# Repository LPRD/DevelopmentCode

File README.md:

# DevelopmentCode
A place to put all our code for messing around and developing things

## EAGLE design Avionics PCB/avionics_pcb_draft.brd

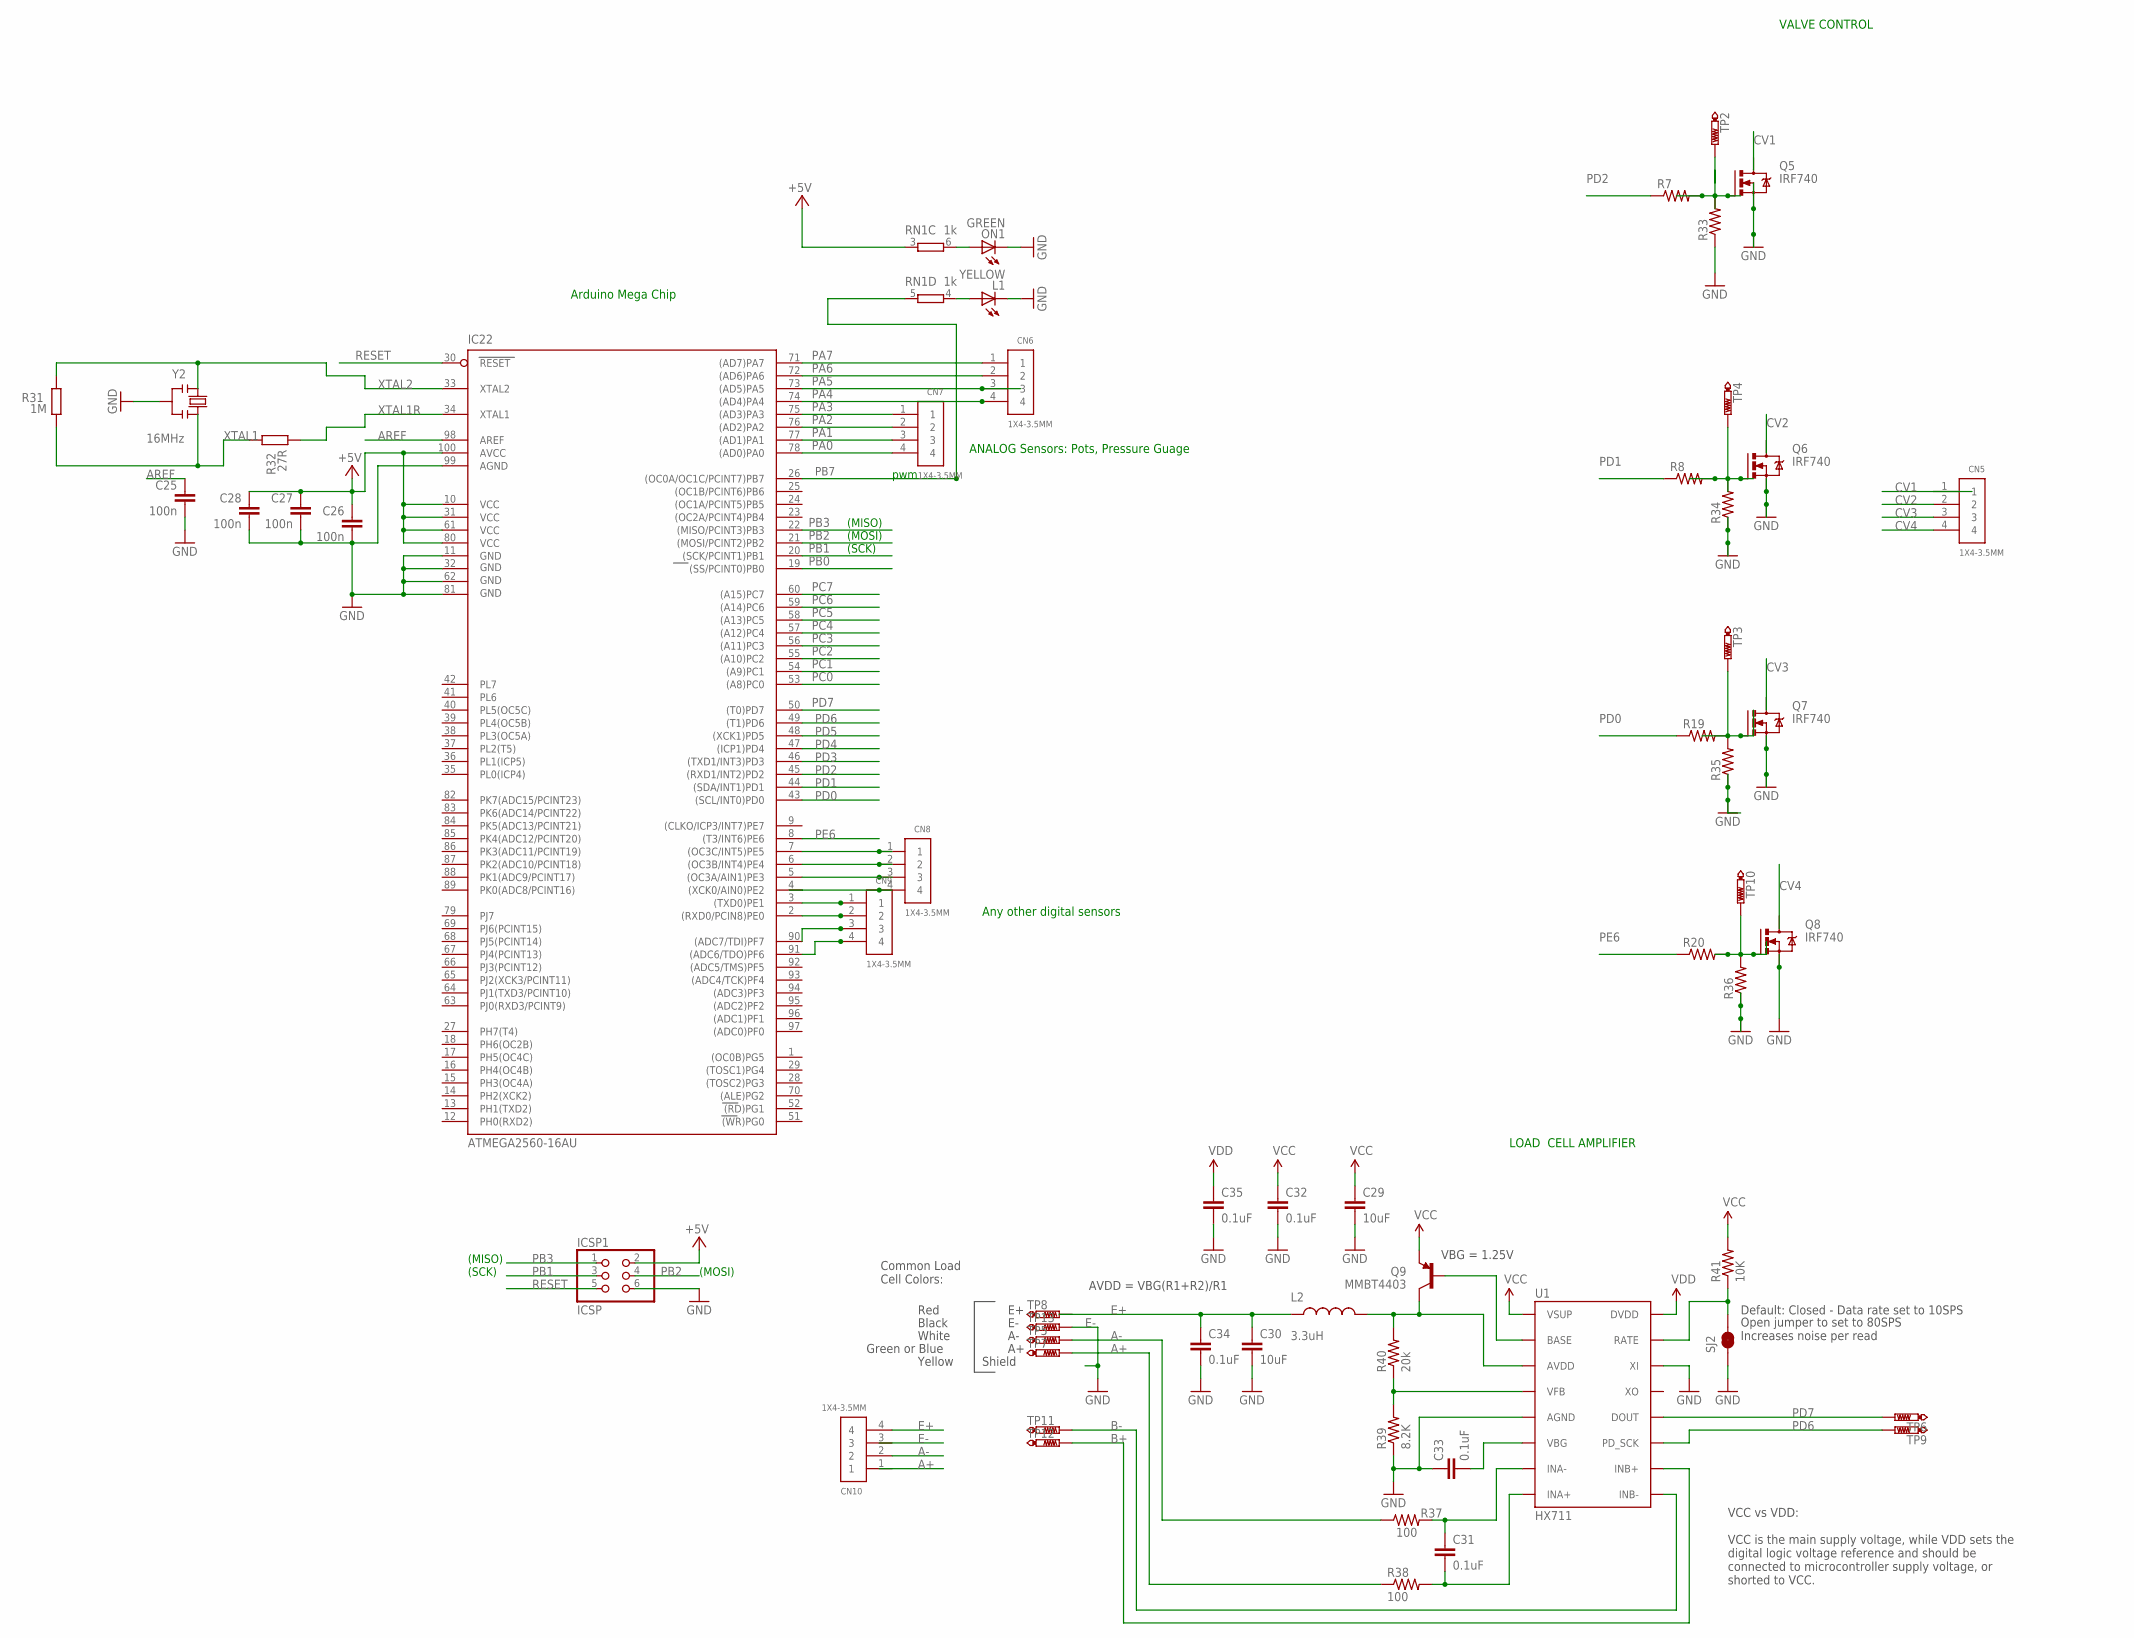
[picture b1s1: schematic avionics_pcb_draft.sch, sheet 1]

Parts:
C25, C26, C27, C28: 100n; C0603-ROUND
C29, C30: 10uF; 1210
C31, C32, C33, C34, C35: 0.1uF; 0603-CAP
CN5, CN6, CN7, CN8, CN9, CN10: 1X4-3.5MM; 1X04-3.5MM
IC22: ATMEGA2560-16AU; TQFP100
ICSP1: ICSP; 2X03
L1: YELLOW; CHIP-LED0805
L2: 3.3uH; 0805
ON1: GREEN; CHIP-LED0805
Q5, Q6, Q7, Q8: IRF740; TO220BV
Q9: MMBT4403; SOT23-3
R7, R8, R19, R20, R33, R34, R35, R36: R-US_R0805; R0805
R31: 1M; R0603-ROUND
R32: 27R; R0603-ROUND
R37, R38: 100; 0603-RES
R39: 8.2K; 0603-RES
R40: 20k; 0603-RES
R41: 10K; 0603-RES
RN1: 1k; CAY16
SJ2: JUMPER-PAD-2-NC_BY_TRACE; PAD-JUMPER-2-NC_BY_TRACE_YES_SILK
TP2, TP3, TP4, TP5, TP6, TP7, TP8, TP9, TP10, TP11, TP12, TP13: PTR1B1,27; B1,27
U1: HX711; SO16
Y2: 16MHz; RESONATOR

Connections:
+5V: C26.1, C27.1, C28.1, IC22.10 (VCC), IC22.31 (VCC1), IC22.61 (VCC2), IC22.80 (VCC3), IC22.100 (AVCC), ICSP1.2, RN1.3 (1); also elsewhere on the board
A+: R38.1, TP7.TP
A-: CN10.2, R37.1, TP5.TP
AREF: C25.1, IC22.98 (AREF)
B+: TP12.TP, U1.10 (INB+)
B-: TP11.TP, U1.9 (INB-)
CV1: CN5.1
CV2: CN5.2
CV3: CN5.3
CV4: CN5.4
E+: C30.1, C34.1, CN10.4, L2.1, TP8.TP
E-: TP13.TP
GND: C25.2, C26.2, C27.2, C28.2, C29.2, C30.2, C32.2, C33.1, C34.2, C35.2, IC22.11 (GND), IC22.32 (GND1), IC22.62 (GND2), IC22.81 (GND3), IC22.99 (AGND), ICSP1.6, L1.C, ON1.C, Q5.S, Q6.S, Q7.S, Q8.S, R33.1, R34.1, R39.1, SJ2.1, U1.5 (AGND), U1.14 (XI), Y2.2; also elsewhere on the board
unnamed: CN8.1, IC22.7 ((OC3C/INT5)PE5)
unnamed: CN8.2, IC22.6 ((OC3B/INT4)PE4)
unnamed: CN8.3, IC22.5 ((OC3A/AIN1)PE3)
unnamed: CN8.4, IC22.4 ((XCK0/AIN0)PE2)
unnamed: Q5.G, R7.2, R33.2
unnamed: Q6.G, R8.2, R34.2
unnamed: CN9.1, IC22.3 ((TXD0)PE1)
unnamed: CN9.2, IC22.2 ((RXD0/PCIN8)PE0)
unnamed: CN9.3, IC22.90 ((ADC7/TDI)PF7)
unnamed: CN9.4, IC22.91 ((ADC6/TDO)PF6)
unnamed: Q7.G, R19.2, R35.2, TP3.TP
unnamed: Q8.G, R20.2, R36.2, TP10.TP
unnamed: ON1.A, RN1.6 (2)
unnamed: L1.A, RN1.4 (1)
unnamed: Q9.1 (B), U1.2 (BASE)
unnamed: R39.2, R40.1, U1.4 (VFB)
unnamed: C33.2, U1.6 (VBG)
unnamed: L2.2, Q9.3 (C), R40.2, U1.3 (AVDD)
unnamed: R41.1, SJ2.2, U1.15 (RATE)
unnamed: C31.1, R37.2, U1.7 (INA-)
unnamed: C31.2, R38.2, U1.8 (INA+)
PA0: CN7.4, IC22.78 ((AD0)PA0)
PA1: CN7.3, IC22.77 ((AD1)PA1)
PA2: CN7.2, IC22.76 ((AD2)PA2)
PA3: CN7.1, IC22.75 ((AD3)PA3)
PA4: CN6.4, IC22.74 ((AD4)PA4)
PA5: CN6.3, IC22.73 ((AD5)PA5)
PA6: CN6.2, IC22.72 ((AD6)PA6)
PA7: CN6.1, IC22.71 ((AD7)PA7)
PB0: IC22.19 ((SS/PCINT0)PB0)
PB1: IC22.20 ((SCK/PCINT1)PB1), ICSP1.3
PB2: IC22.21 ((MOSI/PCINT2)PB2), ICSP1.4
PB3: IC22.22 ((MISO/PCINT3)PB3), ICSP1.1
PB7: IC22.26 ((OC0A/OC1C/PCINT7)PB7), RN1.5 (2)
PC0: IC22.53 ((A8)PC0)
PC1: IC22.54 ((A9)PC1)
PC2: IC22.55 ((A10)PC2)
PC3: IC22.56 ((A11)PC3)
PC4: IC22.57 ((A12)PC4)
PC5: IC22.58 ((A13)PC5)
PC6: IC22.59 ((A14)PC6)
PC7: IC22.60 ((A15)PC7)
PD0: IC22.43 ((SCL/INT0)PD0), R19.1
PD1: IC22.44 ((SDA/INT1)PD1), R8.1
PD2: IC22.45 ((RXD1/INT2)PD2), R7.1
PD3: IC22.46 ((TXD1/INT3)PD3); also elsewhere on the board
PD4: IC22.47 ((ICP1)PD4); also elsewhere on the board
PD5: IC22.48 ((XCK1)PD5); also elsewhere on the board
PD6: IC22.49 ((T1)PD6), TP9.TP, U1.11 (PD_SCK)
PD7: IC22.50 ((T0)PD7), TP6.TP, U1.12 (DOUT)
PE6: IC22.8 ((T3/INT6)PE6), R20.1
RESET: IC22.30 (RESET), ICSP1.5
VCC: C29.1, C32.1, Q9.2 (E), R41.2, U1.1 (VSUP)
VDD: C35.1, U1.16 (DVDD)
XTAL1: R31.1, R32.2, Y2.3
XTAL1R: IC22.34 (XTAL1), R32.1
XTAL2: IC22.33 (XTAL2), R31.2, Y2.1

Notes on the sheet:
(SCK)
(MISO)
(MOSI)
pwm
VBG = 1.25V
AVDD = VBG(R1+R2)/R1
Default: Closed - Data rate set to 10SPS
Open jumper to set to 80SPS Increases noise per read
Red
Black
White
Green or Blue
Common Load Cell Colors:
Shield
Yellow
VCC vs VDD: VCC is the main supply voltage, while VDD sets the digital logic voltage reference and should be connected to microcontroller supply voltage, or shorted to VCC.
Arduino Mega Chip
LOAD CELL AMPLIFIER
VALVE CONTROL
ANALOG Sensors: Pots, Pressure Guage
Any other digital sensors

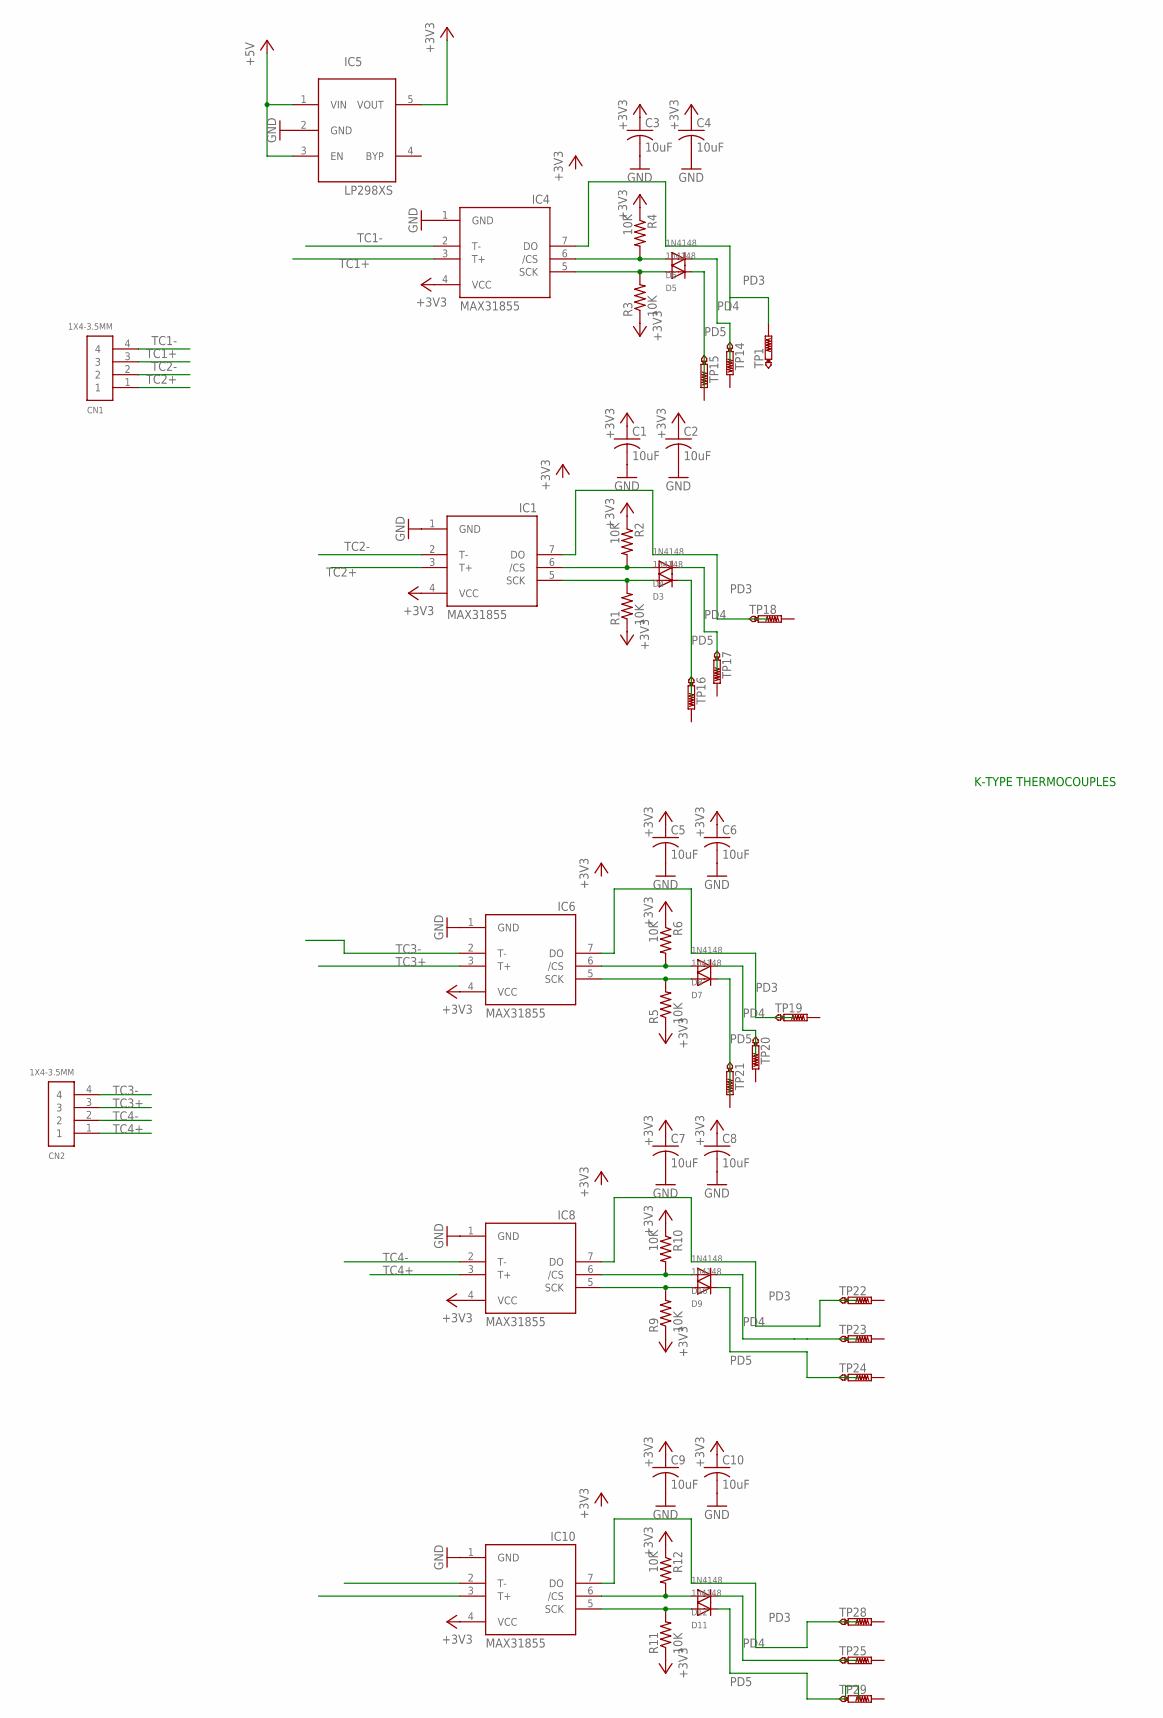
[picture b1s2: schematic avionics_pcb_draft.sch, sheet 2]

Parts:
C1, C2, C3, C4, C5, C6, C7, C8, C9, C10: 10uF; C0805K
CN1, CN2: 1X4-3.5MM; 1X04-3.5MM
D3, D5, D7, D9, D11: 1n4148; SOD-323F
D4, D6, D8, D10, D12: 1N4148; SOD-323F
IC1, IC4, IC6, IC8, IC10: MAX31855; SO08
IC5: LP298XS; SOT23-5L
R1, R2, R3, R4, R5, R6, R9, R10, R11, R12: 10K; R0805
TP1, TP14, TP15, TP16, TP17, TP18, TP19, TP20, TP21, TP22, TP23, TP24, TP25, TP28, TP29: PTR1B1,27; B1,27

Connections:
+3V3: C1.1, C2.1, C3.1, C4.1, C5.1, C6.1, C7.1, C8.1, C9.1, C10.1, IC1.4 (VCC), IC4.4 (VCC), IC5.5 (VOUT), IC6.4 (VCC), IC8.4 (VCC), IC10.4 (VCC), R1.1, R2.1, R3.1, R4.1, R5.1, R6.1, R9.1, R10.1, R11.1, R12.1
+5V: IC5.1 (VIN), IC5.3 (EN); also elsewhere on the board
CS1: D4.A, IC1.6 (/CS), R2.2
CS2: D6.A, IC4.6 (/CS), R4.2
CS3: D8.A, IC6.6 (/CS), R6.2
CS4: D10.A, IC8.6 (/CS), R10.2
CS5: D12.A, IC10.6 (/CS), R12.2
GND: C1.2, C2.2, C3.2, C4.2, C5.2, C6.2, C7.2, C8.2, C9.2, C10.2, IC1.1 (GND), IC4.1 (GND), IC5.2 (GND), IC6.1 (GND), IC8.1 (GND), IC10.1 (GND); also elsewhere on the board
PD3: IC1.7 (DO), IC4.7 (DO), IC6.7 (DO), IC8.7 (DO), IC10.7 (DO), TP1.TP; also elsewhere on the board
PD4: D4.C, D6.C, D8.C, D10.C, D12.C; also elsewhere on the board
PD5: D3.C, D5.C, D7.C, D9.C, D11.C; also elsewhere on the board
SCK1: D3.A, IC1.5 (SCK), R1.2
SCK2: D5.A, IC4.5 (SCK), R3.2
SCK3: D7.A, IC6.5 (SCK), R5.2
SCK4: D9.A, IC8.5 (SCK), R9.2
SCK5: D11.A, IC10.5 (SCK), R11.2
TC1+: CN1.3, IC4.3 (T+)
TC1-: CN1.4, IC4.2 (T-)
TC2+: CN1.1, IC1.3 (T+)
TC2-: CN1.2, IC1.2 (T-)
TC3+: CN2.3, IC6.3 (T+)
TC3-: CN2.4, IC6.2 (T-)
TC4+: CN2.1, IC8.3 (T+)
TC4-: CN2.2, IC8.2 (T-)

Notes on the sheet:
K-TYPE THERMOCOUPLES

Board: 2 copper layers, 111 parts (0 on the bottom side), 75 nets, no tracks yet.

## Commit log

2016-05-21 added servoTest
2016-05-21 added skeleton for proportional control loop
2016-06-04 Added proportional control loop
2016-06-11 PID control implemented
2016-06-25 Modified for new servos
2016-06-28 Arduino IMU code with circular data buffer
2016-07-01 Now runs on IMU data
2016-10-30 Code that returns angle of potentiometer knob
2016-11-01 Added Force Measurement to Temperature and Pressure Code
2016-11-04 Modified version w/ 2 pressure pins
2016-11-04 Libraries for load cell and thermocouple
2016-11-11 minor fix
2016-11-14 modified for valve test
2016-11-15 initial commit adding macros
2016-11-15 angle offset
2016-11-16 Debug
2016-11-19 send multiple pressure fields and modified baud rate
2016-11-19 Calibrated both potentiometers
2016-11-19 Final version used during pressure test
2017-01-31 Oh my god there are so many updates..... if this commit gets rejected I would not be mad at all...
2017-02-01 Create Eagle
2017-03-20 Adding test programs we used last week for debugging
2017-03-31 Modify pressure test driver to return both angles
2017-06-24 Adding Nick's valve control code
2017-07-15 Update calibration
2018-04-01 Code to test Sensors PCB
2018-05-02 Libraries and test code for RS485

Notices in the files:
parts and their libraries:
SparkFun-Capacitors: Licensing: Creative Commons ShareAlike 4.0 International - https://creativecommons.org/licenses/by-sa/4.0
SparkFun-Aesthetics: Licensing: CC v3.0 Share-Alike You are welcome to use this library for commercial purposes.
